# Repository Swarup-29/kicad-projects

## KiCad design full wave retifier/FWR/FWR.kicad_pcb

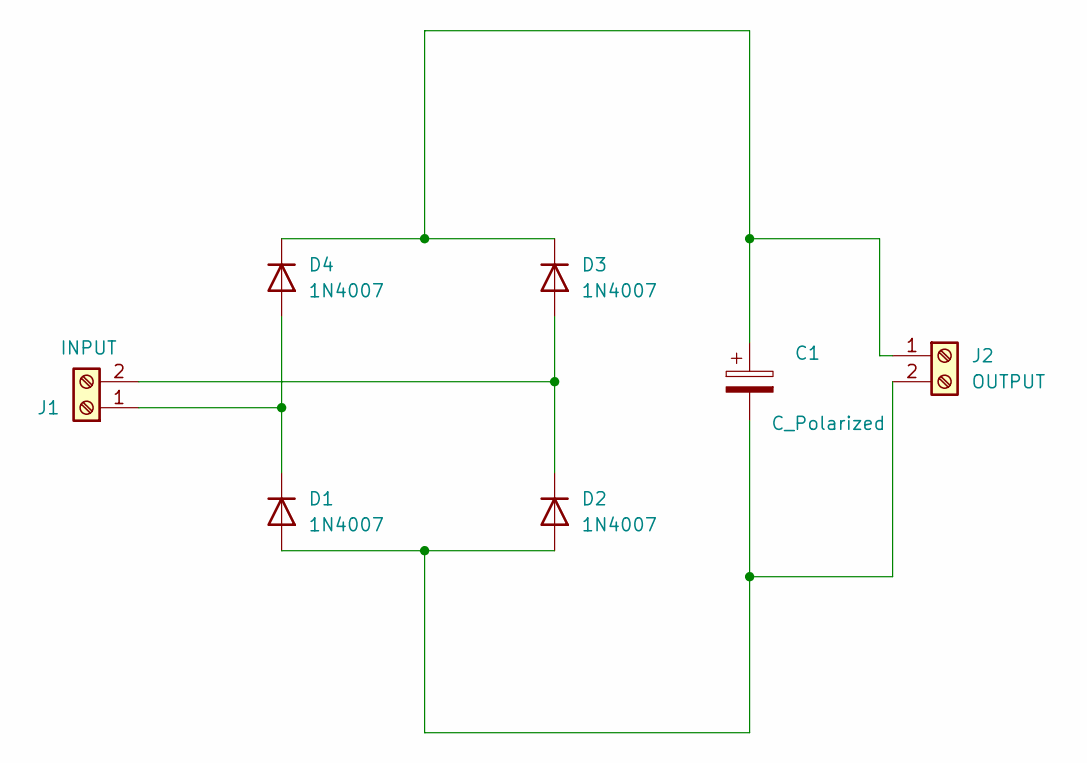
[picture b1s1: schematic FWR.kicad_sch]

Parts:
C1: C_Polarized; CP_Radial_D8.0mm_P3.50mm
D1, D2, D3, D4: 1N4007; D_DO-41_SOD81_P7.62mm_Horizontal
J1: INPUT; TerminalBlock_Phoenix_MKDS-1,5-2_1x02_P5.00mm_Horizontal
J2: OUTPUT; TerminalBlock_Phoenix_MKDS-1,5-2_1x02_P5.00mm_Horizontal

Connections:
unnamed: C1.2, D1.2 (A), D2.2 (A), J2.2
unnamed: D1.1 (K), D4.2 (A), J1.1
unnamed: D2.1 (K), D3.2 (A), J1.2
unnamed: C1.1, D3.1 (K), D4.1 (K), J2.1

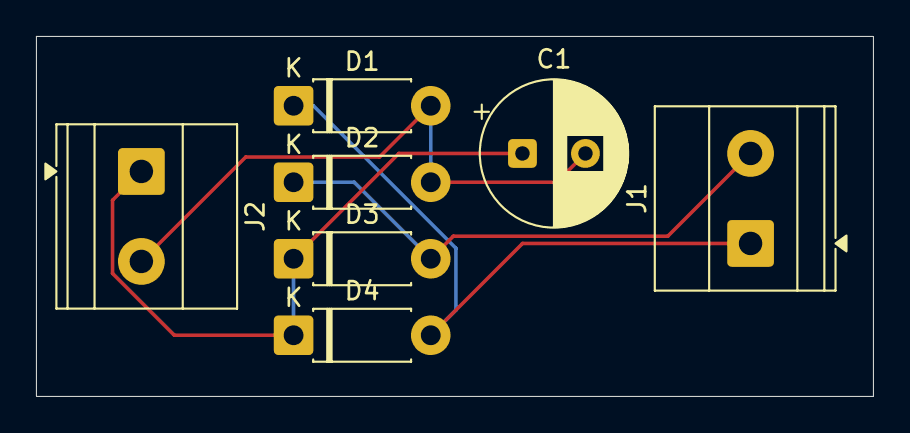
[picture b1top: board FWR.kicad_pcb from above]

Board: 2 copper layers, 46.5 x 20.0 mm, 7 parts (0 on the bottom side), 4 nets.

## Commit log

2026-03-30 new files
2026-03-30 Add initial content to README.md
